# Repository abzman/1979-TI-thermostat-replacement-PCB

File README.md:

# 1979-TI-thermostat-replacement-PCB
replaces the PCB in an old thermostat with one that has an esp32 onboard and other upgrades

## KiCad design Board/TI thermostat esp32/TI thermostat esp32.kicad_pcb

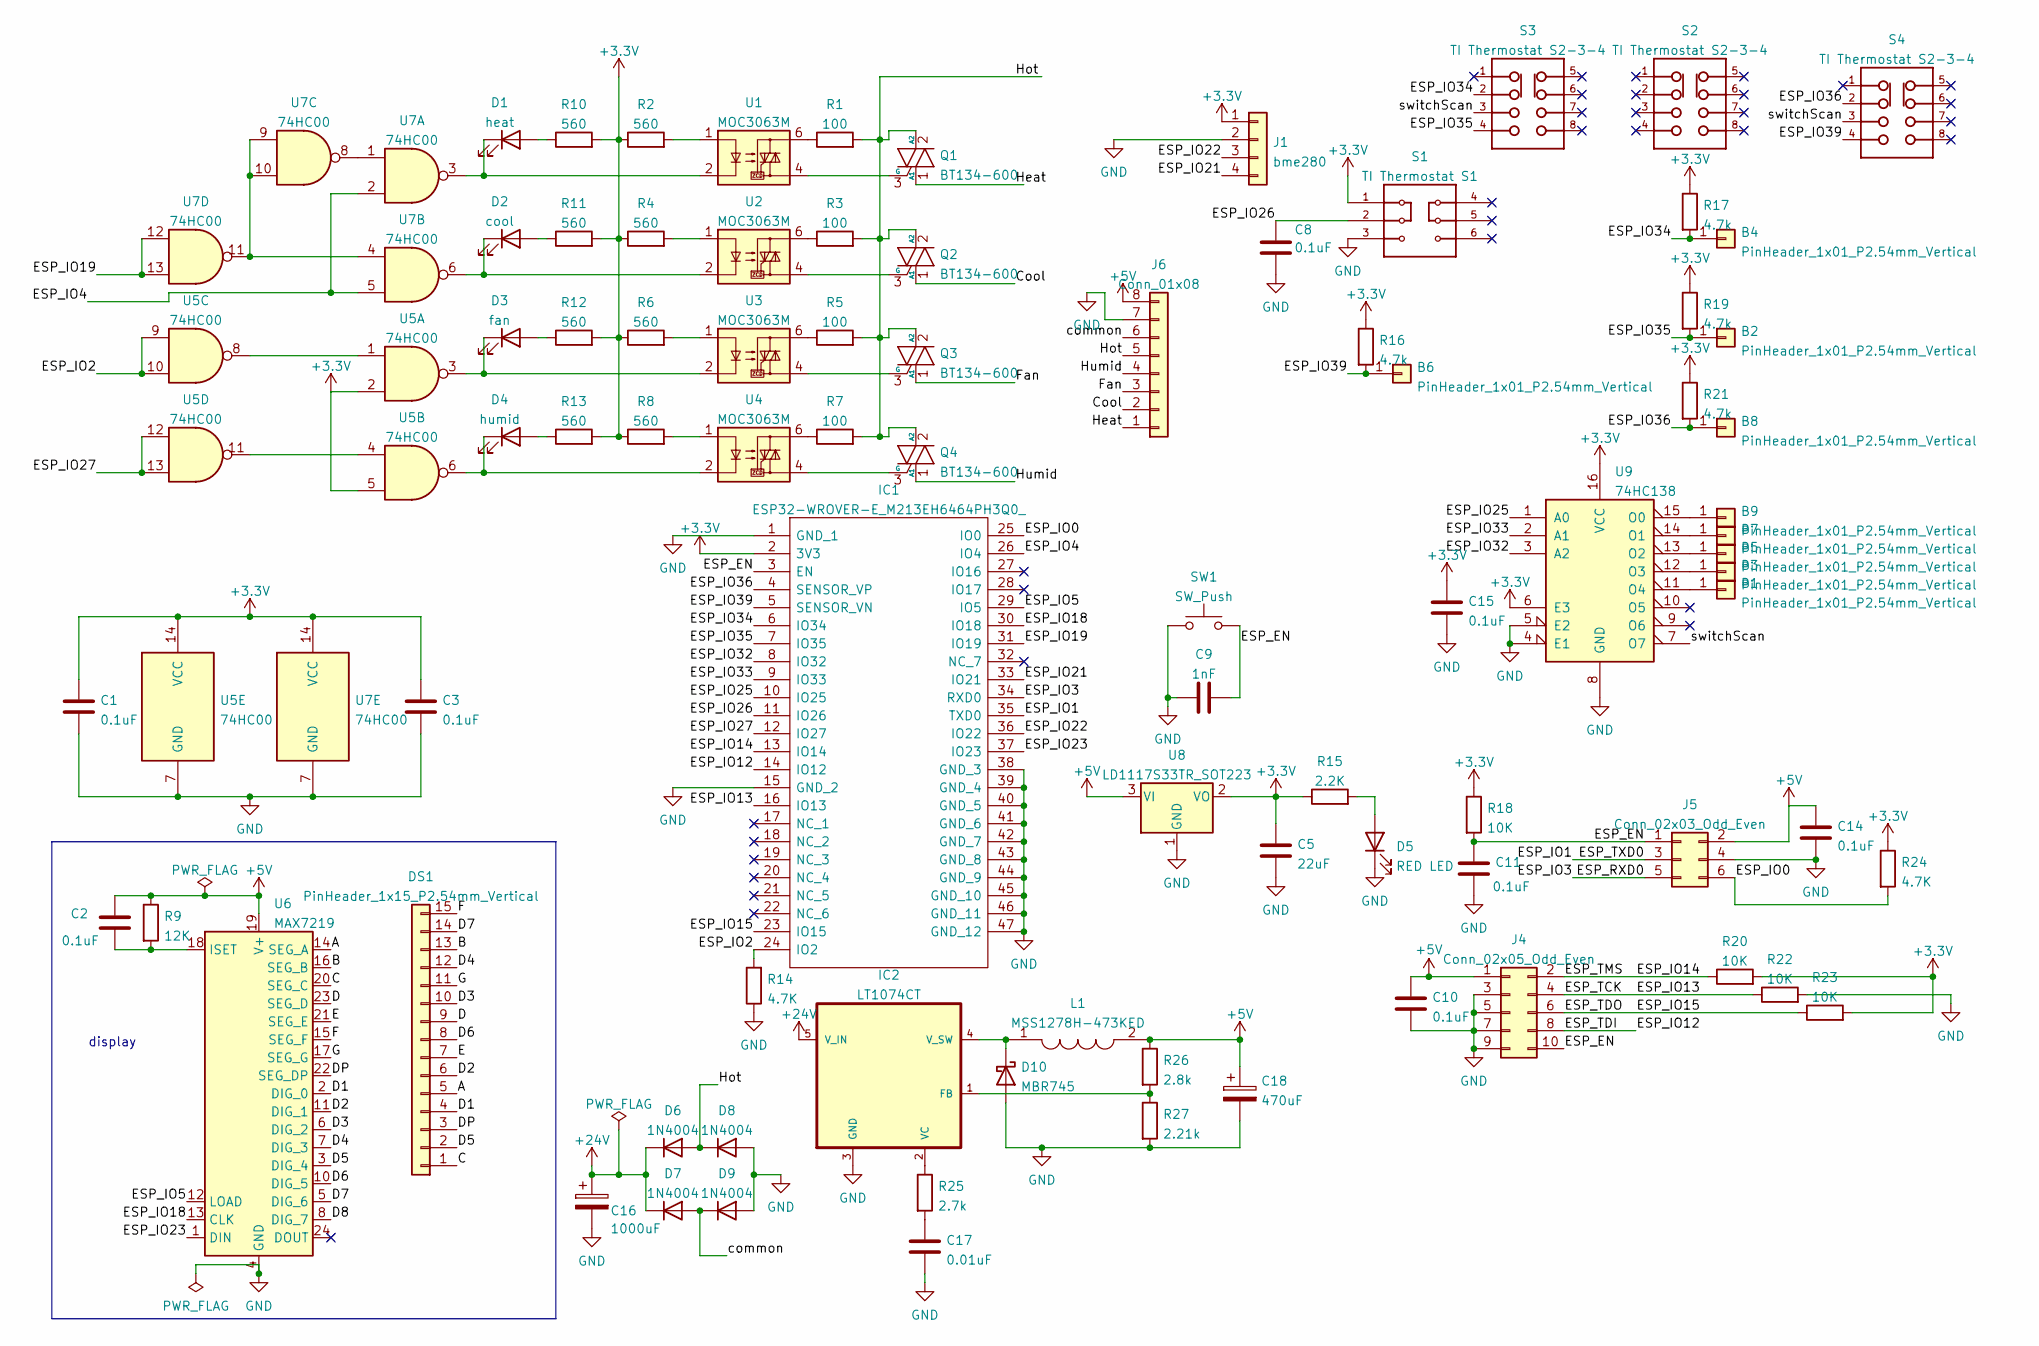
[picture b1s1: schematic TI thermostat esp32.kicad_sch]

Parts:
B1, B2, B3, B4, B5, B6, B7, B8, B9: PinHeader_1x01_P2.54mm_Vertical
C1, C2, C3, C8, C10, C11, C14, C15: 0.1uF; C_0603_1608Metric
C5: 22uF; CP_Radial_D5.0mm_P2.00mm
C9: 1nF; C_0603_1608Metric
C16: 1000uF; CP_Radial_D7.5mm_P2.50mm
C17: 0.01uF; C_0603_1608Metric
C18: 470uF; CP_Radial_D7.5mm_P2.50mm
D1: heat; LED_0603_1608Metric
D2: cool; LED_0603_1608Metric
D3: fan; LED_0603_1608Metric
D4: humid; LED_0603_1608Metric
D5: RED LED; LED_0603_1608Metric
D6, D7, D8, D9: 1N4004; D_SMA
D10: MBR745; TO-220-2_Horizontal_TabUp
DS1: PinHeader_1x15_P2.54mm_Vertical
IC1: ESP32-WROVER-E_M213EH6464PH3Q0_; ESP32WROVEREM213EH6464PH3Q0; Mouser Part Number 356-ESP32WRVE26464PC
IC2: LT1074CT; TO220_5L
J1: bme280; PinHeader_1x04_P2.54mm_Vertical
J4: Conn_02x05_Odd_Even; PinHeader_2x05_P2.54mm_Horizontal
J5: Conn_02x03_Odd_Even; PinHeader_2x03_P2.54mm_Horizontal
J6: Conn_01x08; PhoenixContact_MC_1,5_8-G-3.81_1x08_P3.81mm_Horizontal
L1: MSS1278H-473KED; INDPM120120X805N; Mouser Part Number 994-MSS1278H-473KED
Q1, Q2, Q3, Q4: BT134-600; TO-126-3_Horizontal_TabDown
R1, R3, R5, R7: 100; R_0603_1608Metric
R2, R4, R6, R8, R10, R11, R12, R13: 560; R_0603_1608Metric
R9: 12K; R_0603_1608Metric
R14, R24: 4.7K; R_0603_1608Metric
R15: 2.2K; R_0603_1608Metric
R16, R17, R19, R21: 4.7k; R_0603_1608Metric
R18, R20, R22, R23: 10K; R_0603_1608Metric
R25: 2.7k; R_0603_1608Metric
R26: 2.8k; R_0603_1608Metric
R27: 2.21k; R_0603_1608Metric
S1: TI Thermostat S1
S2, S3, S4: TI Thermostat S2-3-4
SW1: SW_Push; SW_Tactile_SPST_Angled_PTS645Vx39-2LFS
U1, U2, U3, U4: MOC3063M; DIP-6_W7.62mm
U5, U7: 74HC00; SOIC-14_3.9x8.7mm_P1.27mm
U6: MAX7219; SOP-24_7.5x15.4mm_P1.27mm
U8: LD1117S33TR_SOT223; SOT-223-3_TabPin2
U9: 74HC138; SOIC-16_3.9x9.9mm_P1.27mm

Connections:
+3V3: C1.1, C3.1, C5.1, C15.1, IC1.2 (3V3), J1.1, R2.1, R4.1, R6.1, R8.1, R10.2, R11.2, R12.2, R13.2, R15.1, R16.1, R17.1, R18.1, R19.1, R20.2, R21.1, R23.2, R24.1, S1.1, U5.2, U5.5, U5.14 (VCC), U7.14 (VCC), U8.2 (VO), U9.6 (E3), U9.16 (VCC)
+5V: C2.1, C10.1, C14.1, C18.1, J4.1, J5.2, J6.8, L1.2, R9.1, R26.1, U6.19 (V+), U8.3 (VI)
+24V: C16.1, D6.1 (K), D7.1 (K), IC2.5 (V_IN)
/A: DS1.5, U6.14 (SEG_A)
/B: DS1.13, U6.16 (SEG_B)
/C: DS1.1, U6.20 (SEG_C)
/Cool: J6.2, Q2.1 (A1)
/D: DS1.9, U6.23 (SEG_D)
/D1: DS1.4, U6.2 (DIG_0)
/D2: DS1.6, U6.11 (DIG_1)
/D3: DS1.10, U6.6 (DIG_2)
/D4: DS1.12, U6.7 (DIG_3)
/D5: DS1.2, U6.3 (DIG_4)
/D6: DS1.8, U6.10 (DIG_5)
/D7: DS1.14, U6.5 (DIG_6)
/D8: U6.8 (DIG_7)
/DP: DS1.3, U6.22 (SEG_DP)
/E: DS1.7, U6.21 (SEG_E)
/ESP_EN: C9.2, C11.1, IC1.3 (EN), J4.10, J5.1, R18.2, SW1.2
/ESP_IO0: IC1.25 (IO0), J5.6, R24.2
/ESP_IO1: IC1.35 (TXD0), J5.3
/ESP_IO2: IC1.24 (IO2), R14.2, U5.9, U5.10
/ESP_IO3: IC1.34 (RXD0), J5.5
/ESP_IO4: IC1.26 (IO4), U7.2, U7.5
/ESP_IO5: IC1.29 (IO5), U6.12 (LOAD)
/ESP_IO12: IC1.14 (IO12), J4.8
/ESP_IO13: IC1.16 (IO13), J4.4, R22.1
/ESP_IO14: IC1.13 (IO14), J4.2, R20.1
/ESP_IO15: IC1.23 (IO15), J4.6, R23.1
/ESP_IO18: IC1.30 (IO18), U6.13 (CLK)
/ESP_IO19: IC1.31 (IO19), U7.12, U7.13
/ESP_IO21: IC1.33 (IO21), J1.4
/ESP_IO22: IC1.36 (IO22), J1.3
/ESP_IO23: IC1.37 (IO23), U6.1 (DIN)
/ESP_IO25: IC1.10 (IO25), U9.1 (A0)
/ESP_IO26: C8.1, IC1.11 (IO26), S1.2
/ESP_IO27: IC1.12 (IO27), U5.12, U5.13
/ESP_IO32: IC1.8 (IO32), U9.3 (A2)
/ESP_IO33: IC1.9 (IO33), U9.2 (A1)
/ESP_IO34: B4.1, IC1.6 (IO34), R17.2, S3.2
/ESP_IO35: B2.1, IC1.7 (IO35), R19.2, S3.4
/ESP_IO36: B8.1, IC1.4 (SENSOR_VP), R21.2, S4.2
/ESP_IO39: B6.1, IC1.5 (SENSOR_VN), R16.2, S4.4
/F: DS1.15, U6.15 (SEG_F)
/Fan: J6.3, Q3.1 (A1)
/G: DS1.11, U6.17 (SEG_G)
/Heat: J6.1, Q1.1 (A1)
/Hot: D6.2 (A), D8.1 (K), J6.5, Q1.2 (A2), Q2.2 (A2), Q3.2 (A2), Q4.2 (A2), R1.2, R3.2, R5.2, R7.2
/Humid: J6.4, Q4.1 (A1)
/common: D7.2 (A), D9.1 (K), J6.6
/switchScan: S3.3, S4.3, U9.7 (O7)
GND: C1.2, C3.2, C5.2, C8.2, C9.1, C10.2, C11.2, C14.2, C15.2, C16.2, C17.2, C18.2, D5.1 (K), D8.2 (A), D9.2 (A), D10.2 (A), IC1.1 (GND_1), IC1.15 (GND_2), IC1.38 (GND_3), IC1.39 (GND_4), IC1.40 (GND_5), IC1.41 (GND_6), IC1.42 (GND_7), IC1.43 (GND_8), IC1.44 (GND_9), IC1.45 (GND_10), IC1.46 (GND_11), IC1.47 (GND_12), IC2.3 (GND), J1.2, J4.3, J4.5, J4.7, J4.9, J5.4, J6.7, R14.1, R22.2, R27.2, S1.3, SW1.1, U5.7 (GND), U6.4 (GND), U6.9 (GND), U7.7 (GND), U8.1 (GND), U9.4 (E1), U9.5 (E2), U9.8 (GND)
unnamed: B1.1, U9.11 (O4)
unnamed: B3.1, U9.12 (O3)
unnamed: B5.1, U9.13 (O2)
unnamed: B7.1, U9.14 (O1)
unnamed: B9.1, U9.15 (O0)
unnamed: C2.2, R9.2, U6.18 (ISET)
unnamed: C17.1, R25.2
unnamed: D1.1 (K), U1.2, U7.3
unnamed: D1.2 (A), R10.1
unnamed: D2.1 (K), U2.2, U7.6
unnamed: D2.2 (A), R11.1
unnamed: D3.1 (K), U3.2, U5.3
unnamed: D3.2 (A), R12.1
unnamed: D4.1 (K), U4.2, U5.6
unnamed: D4.2 (A), R13.1
unnamed: D5.2 (A), R15.2
unnamed: D10.1 (K), IC2.4 (V_SW), L1.1
unnamed: IC2.1 (FB), R26.2, R27.1
unnamed: IC2.2 (VC), R25.1
unnamed: Q1.3 (G), U1.4
unnamed: Q2.3 (G), U2.4
unnamed: Q3.3 (G), U3.4
unnamed: Q4.3 (G), U4.4
unnamed: R1.1, U1.6
unnamed: R2.2, U1.1
unnamed: R3.1, U2.6
unnamed: R4.2, U2.1
unnamed: R5.1, U3.6
unnamed: R6.2, U3.1
unnamed: R7.1, U4.6
unnamed: R8.2, U4.1
unnamed: U5.1, U5.8
unnamed: U5.4, U5.11
unnamed: U7.1, U7.8
unnamed: U7.4, U7.9, U7.10, U7.11

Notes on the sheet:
display

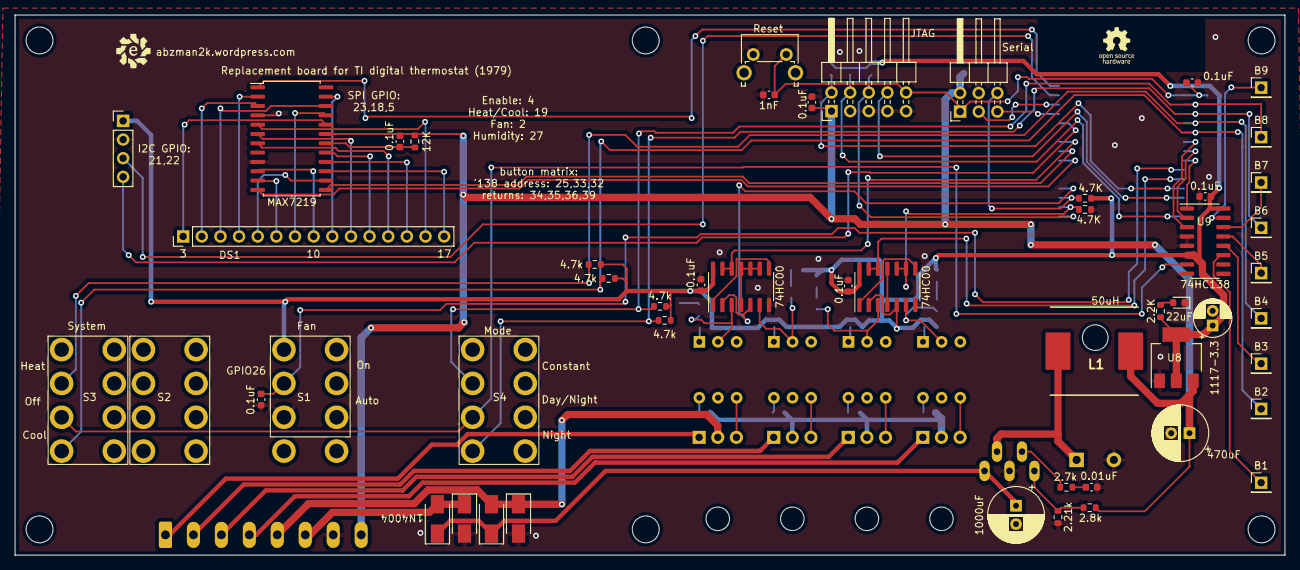
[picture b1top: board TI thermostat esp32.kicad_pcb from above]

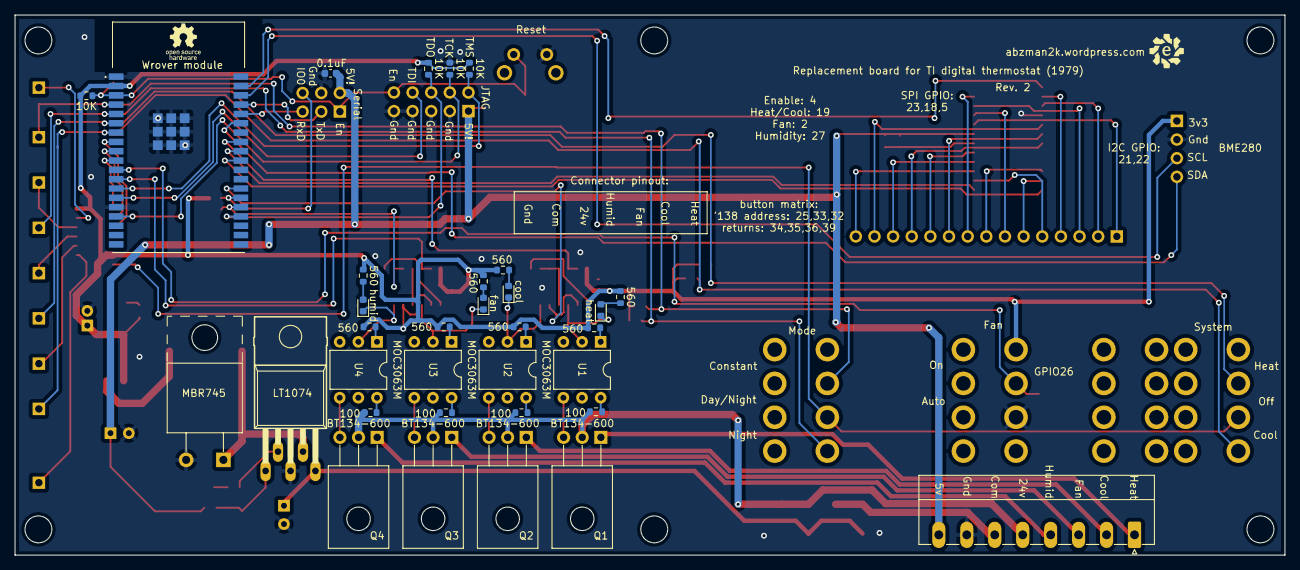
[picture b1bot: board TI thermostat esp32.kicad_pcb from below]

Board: 2 copper layers, 173.0 x 73.6 mm, 91 parts (33 on the bottom side), 86 nets.

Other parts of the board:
REF1, REF2, REF3, REF4, REF5, REF6: MountingHole_TI_Thermostat

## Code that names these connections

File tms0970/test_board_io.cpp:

// Simulates the schematic's gate network and checks levels_for() against it.
#include <stdio.h>
#include "board_io.h"
using board::Outputs;
struct Triacs { bool heat, cool, fan, humid; };
// 74HC00 stages exactly as drawn; optotriac LEDs are active-low (anode on +3V3).
static Triacs hardware(int io4, int io19, int io2, int io27) {
  auto nand = [](int a, int b) { return !(a && b); };
  int u7d = nand(io19, io19), u7c = nand(u7d, u7d);          // inverter, inverter
  int heat_n = nand(u7c, io4), cool_n = nand(u7d, io4);
  int fan_n = nand(nand(io2, io2), 1), humid_n = nand(nand(io27, io27), 1);
  return {!heat_n, !cool_n, !fan_n, !humid_n};
}
int main() {
  int bad = 0, both = 0;
  for (int m = 0; m < 16; m++) {
    Outputs o; o.heat = m & 1; o.cool = m & 2; o.fan = m & 4; o.humid = m & 8;
    auto p = board::levels_for(o);
    Triacs t = hardware(p.enable, p.heat_select, p.fan_pin, p.humid_pin);
    bool eh = o.heat && !o.cool, ec = o.cool && !o.heat;      // both requested -> both off
    if (t.heat != eh || t.cool != ec || t.fan != o.fan || t.humid != o.humid) { bad++; printf("MISMATCH req=%x\n", m); }
  }
  for (int a = 0; a < 2; a++) for (int b = 0; b < 2; b++)      // hardware lockout for ANY IO4/IO19 state
    for (int c = 0; c < 2; c++) for (int d = 0; d < 2; d++) { auto t = hardware(a, b, c, d); if (t.heat && t.cool) both++; }
  printf("request->triac check: %s\n", bad ? "FAIL" : "all 16 request combinations produce the intended triac states");
  printf("heat+cool simultaneously possible for any of the 16 pin states: %s\n", both ? "YES (bad)" : "no");
  Triacs rst = hardware(0, 0, 0, 1);
  printf("pins IO4=0 IO19=0 IO2=0 IO27=1 (what a reset with IO2 pulled low looks like): fan %s, humid %s\n", rst.fan ? "ON" : "off", rst.humid ? "ON" : "off");
}

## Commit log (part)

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2022-01-25 first commit (board rev1)
2022-02-09 rev2 pcb and layout plus test code
2022-02-10 added bme test code
2022-11-25 added gitignore
